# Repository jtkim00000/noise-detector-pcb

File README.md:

# Noise Detector PCB

This document is an in-depth description and documentation of the Noise Detector PCB which I designed from scratch.

## Table of Contents
- [Overview](#overview)
- [Circuit](#circuit)
  - [Power Supply](#power-supply) 
  - [Microphone and Amplifier](#microphone-and-amplifier)
  - [Peak Detector](#peak-detector)
  - [RC Time Delay](#rc-time-delay)
  - [3-stage Comparator](#3-stage-comparator)
  - [Final Circuit](#final-circuit)
- [PCB](#pcb)

## Overview

The following documentation is a full explanation and walk through of my Noise Detector PCB, an analog circuit. 

The circuit includes an analog signal chain (amplification → peak detection → timed delay → threshold comparison). The components include a condenser microphone, LM358 op-amp, LM311 comparator, and a Schmitt Trigger Inverter. 

The design includes an NMOS-switched peak detector, an RC hold time delay circuit to capture audio peak for a set time, and a 3-level voltage comparator network that connects to a 3-level LED volume indicator.

## Circuit

### Power Supply

All components in this circuit require a +9V, GND, and -9V. This is created by wiring two 9V batteries in series, creating an 18V difference between the two, and setting the GND to the point inbetween the batteries, creating +9V, 0V, and -9V. 

### Microphone and Amplifier

The Condenser Microphone simply converts sound into an electric signal. Sound comes into the microphone and vibrates a diaphragm which creates an induced current. This current is then used to compute a voltage which is the signal we are measuring.

However, for this circuit component the voltage signal amplitude is far too small to read, thus we need to amplify the signal. For this I used an inverting amplifier based on an LM358 OpAmp. The amplification is defined as R2/R1, where R2 is the feedback resistor. This is also known as the gain, in which I chose to use a gain of 100k/47 = 2127.66.  

### Peak Detector

The peak detector module is designed to capture the maximum amplitude of voltage input from a time-varying signal. It does this by using an LM358 OpAmp, which when applying nodal analysis, we can considered the + and - inputs to have the same voltage. In this way connecting the output of the OpAmp to the inverting input creates a voltage follower circuit. 

We can extend the design of the voltage follower input by adding a capacitor and diode such that the capacitor charges up to match the maximum voltage amplitude, but has no route to drain on its own. We add an NMOS switch to drain the capacitor, acting as a reset. 

### RC Time Delay

The time delay module provides a controlled delay signal using an RC circuit. This provides our circuit with a fixed time which controls the duration the LEDs remain lit after the initial trigger.

The time delay first uses a comparator that compares the input signal to a voltage threshold. If the signal exceeds that threshold, the time delay begins. 

By default the capacitor is fully charged as it has an RC path to Vs, our voltage source. When the threshold is met, an NMOS is switched on, connecting the capacitor to GND, instantly draining it. The capacitor then takes time to recharge, which can be modeled by a commonly known differential equation. 

The output of this time delay is fed into a schmitt trigger inverter, which outputs high while the capacitor voltage is below a threshold. I fed this into another inverter, such that the output can reset the peak detector once the RC is above that threshold. 

### 3-stage Comparator

The 3-stage comparator simply uses a resistor/potentiometer network, that acts as a voltage divider, and 3 LM311 high speed comparators to create the module. This compares the output of the peak detector, or our max voltage, and controls a 3-level LED display, indicating volume. 

### Final Circuit

The diagram above describes the analog signal chain used to connect all submodules. The microphone output feeds into the amp, which feeds into the peak detector and time delay. The time delay control the reset of the peak detector and the peak detector output feeds into the comparator. 

The final circuit diagram is shown below

## PCB

The final circuit was then converted into a PCB design in KiCAD. The design uses a 2-layer PCB, and follows the same circuit design described as above. The PCB passed all design rules checks. The majority of optimizations were in reduce trace length.

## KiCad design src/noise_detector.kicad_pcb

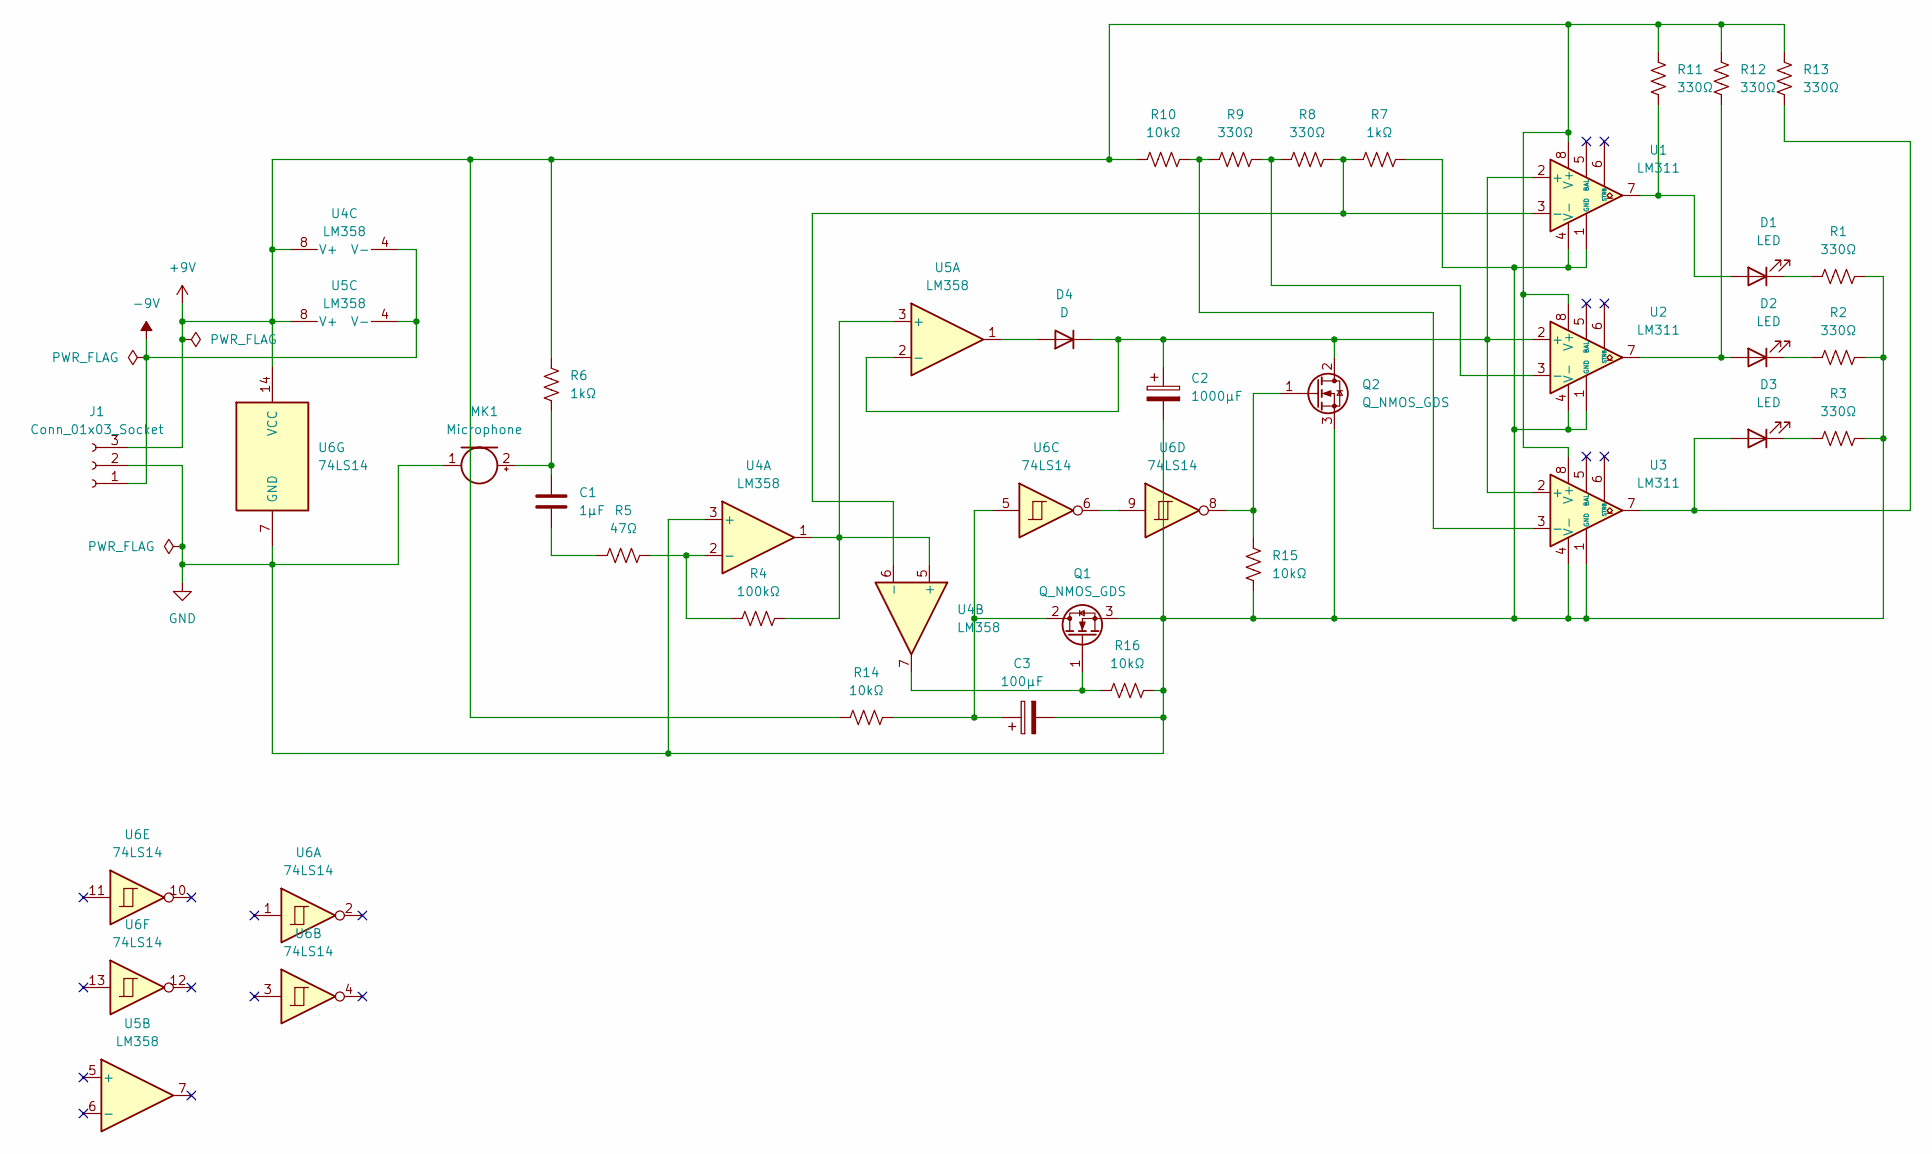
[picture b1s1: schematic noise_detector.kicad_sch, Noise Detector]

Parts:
C1: 1µF; C_Disc_D5.0mm_W2.5mm_P2.50mm
C2: 1000µF; CP_Radial_D10.0mm_P5.00mm
C3: 100µF; CP_Radial_D5.0mm_P2.50mm
D1, D2, D3: LED; LED_D5.0mm
D4: D; D_DO-35_SOD27_P7.62mm_Horizontal
J1: Conn_01x03_Socket; PinHeader_1x03_P2.54mm_Vertical
MK1: Microphone
Q1, Q2: Q_NMOS_GDS; TO-220-3_Vertical
R1, R2, R3, R8, R9, R11, R12, R13: 330Ω; R_Axial_DIN0207_L6.3mm_D2.5mm_P7.62mm_Horizontal
R4: 100kΩ; R_Axial_DIN0207_L6.3mm_D2.5mm_P7.62mm_Horizontal
R5: 47Ω; R_Axial_DIN0207_L6.3mm_D2.5mm_P7.62mm_Horizontal
R6, R7: 1kΩ; R_Axial_DIN0207_L6.3mm_D2.5mm_P7.62mm_Horizontal
R10, R14, R15, R16: 10kΩ; R_Axial_DIN0207_L6.3mm_D2.5mm_P7.62mm_Horizontal
U1, U2, U3: LM311; DIP-8_W7.62mm
U4, U5: LM358; DIP-8_W7.62mm
U6: 74LS14; DIP-14_W7.62mm

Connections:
+9V: J1.3, R6.1, R10.2, R11.1, R12.1, R13.1, R14.1, U1.8 (V+), U2.8 (V+), U3.8 (V+), U4.8 (V+), U5.8 (V+), U6.14 (VCC)
-9V: J1.1, U4.4 (V-), U5.4 (V-)
GND: C2.2, C3.2, J1.2, MK1.1 (-), Q1.3 (S), Q2.3 (S), R1.2, R2.2, R3.2, R7.1, R15.2, R16.2, U1.1 (GND), U1.4 (V-), U2.1 (GND), U2.4 (V-), U3.1 (GND), U3.4 (V-), U4.3 (+), U6.7 (GND)
unnamed: C1.1, R5.1
unnamed: D1.2 (A), R11.2, U1.7
unnamed: D1.1 (K), R1.1
unnamed: D2.2 (A), R12.2, U2.7
unnamed: D2.1 (K), R2.1
unnamed: D3.2 (A), R13.2, U3.7
unnamed: D3.1 (K), R3.1
unnamed: D4.2 (A), U5.1
unnamed: C2.1, D4.1 (K), Q2.2 (D), U1.2 (+), U2.2 (+), U3.2 (+), U5.2 (-)
unnamed: C1.2, MK1.2 (+), R6.2
unnamed: C3.1, Q1.2 (D), R14.2, U6.5
unnamed: Q1.1 (G), R16.1, U4.7
unnamed: Q2.1 (G), R15.1, U6.8
unnamed: R7.2, R8.1, U1.3 (-), U4.6 (-)
unnamed: R8.2, R9.1, U2.3 (-)
unnamed: R9.2, R10.1, U3.3 (-)
unnamed: R4.1, R5.2, U4.2 (-)
unnamed: R4.2, U4.1, U4.5 (+), U5.3 (+)
unnamed: U6.6, U6.9

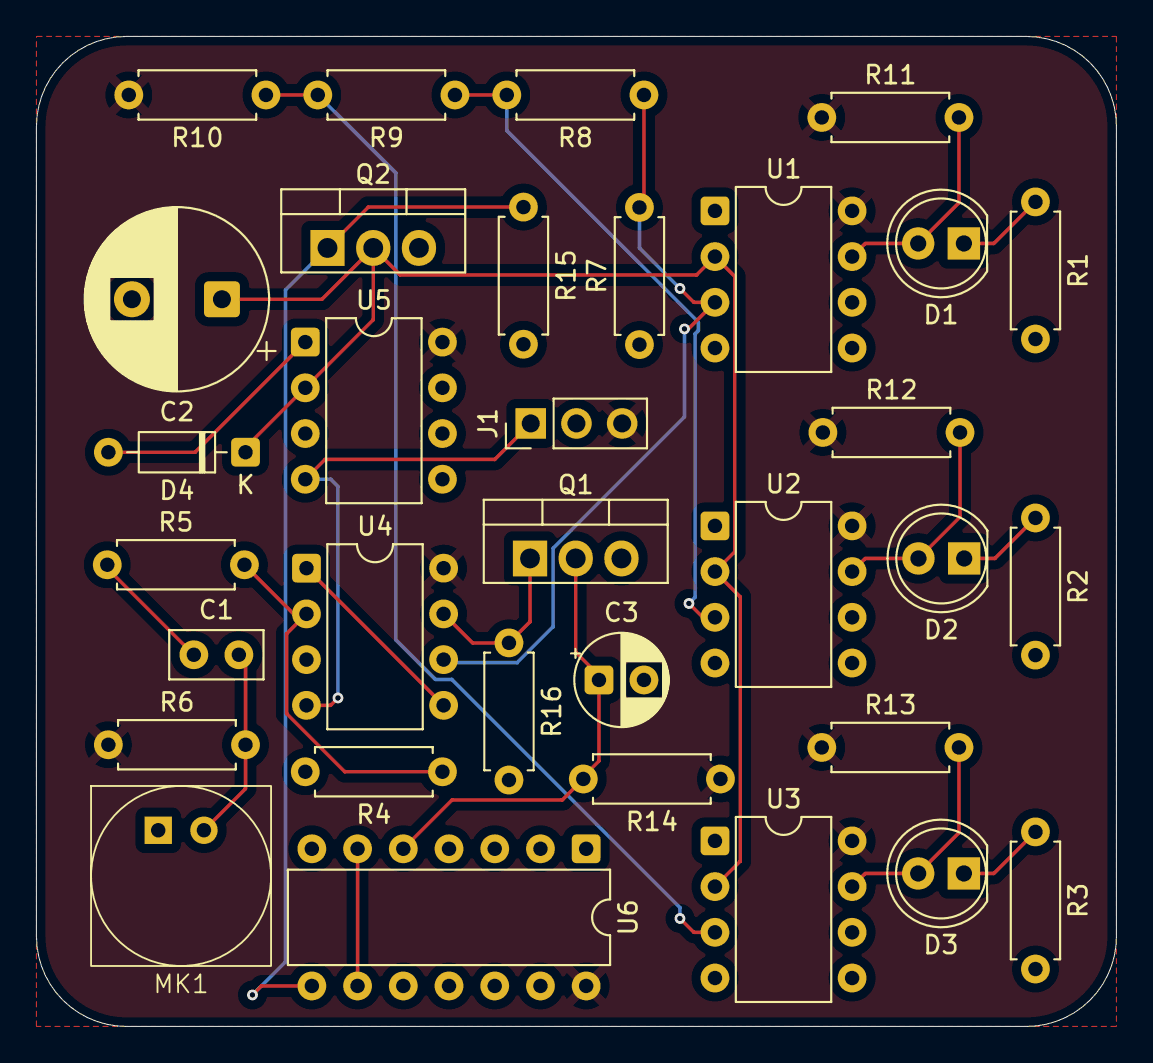
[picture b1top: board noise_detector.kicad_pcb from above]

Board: 2 copper layers, 60.0 x 55.0 mm, 33 parts (0 on the bottom side), 22 nets.

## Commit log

2026-06-23 adding Kicad files
2026-06-24 photo files
2026-06-25 chain diagram
2026-06-25 ignore
